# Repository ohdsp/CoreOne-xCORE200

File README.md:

# [Open Hardware DSP Platform](http://www.ohdsp.org)
## CoreOne-xCORE200
### Revision 2.1

---
# README
### Disclaimer
Copyright Paul Janicki 2019

Licensed under the TAPR Open Hardware License (www.tapr.org/OHL)

This documentation is distributed WITHOUT ANY EXPRESS OR IMPLIED WARRANTY, INCLUDING OF MERCHANTABILITY, SATISFACTORY QUALITY AND FITNESS FOR A PARTICULAR PURPOSE.

### What is this repository?

**Quick summary**

This is Open Hardware DSP Platform CoreOne-xCORE200 Module Revision 2.0. 

This is a less cramped XMOS 200 based DSP and mirocontroller PCB design with USB, SPDIF, I2S/TDM, SPI, I2C, and Ethernet connectivity options.

This repository contains the KiCad design files, manufacturing Gerber/drill files, PDF/drawing files, and relevant documenation for this board.

**Changelog**
Revision 2.1 has the following changes over Revision 2.0:
Added better grounding on power connector only, added extra vias.

Revision 2.0 has the following changes over Revision 1.0:
The ST1S40 regualtors have been replaced with RT7285C parts
The CS2100 clock generator has been removed
The TPS3808 reset circut has been replaced with an NCP308 part
There are now components on the bottom layer to reduce cramping
Third I2S connector removed
Added second I2C and second SPI connectors

### What is the project folder structure?
Most folder names are self explanatory. Starting from the top level: \
*CoreOne*
+ *Bill of Materials*  - This contains the bill of materials in CVS, LibreOffice Calc and XML formats
+ *Drawings* - This contains PDF and SVG Schematic and PCB files
+ *Gerbers* - This contains the PCB Gerbers and drill drawings for manufacture, there is also a zip file ready to send to most manufacturers
+ *JPEGs* - JPEGs of top and bottom views from 3D viewer
+ *KiCad* - This contains the original KiCad schematic and PCB design files
+ *Pick and Place* - This contains pick and place files for top and bottom sides
### How do I get set up?

**Summary of set up**

1. Set your self up a directory on a local disk, something simple will make life easier (eg C:\Electronics on Windows as used here), but anywhere will do just fine.
2. Download the Kicad-Libs from [https://github.com/ohdsp/KiCad-Libs](https://github.com/ohdsp/KiCad-Libs) and place in C:\Electronics\Kicad-Libs (or your chosen folder) 
3. Create a OHDSP subdirectory in C:\Electronics (so C:\Electronics\OHDSP)
3. Download this project to C:\Electronics\OHDSP\uDSP
4. Fire up Kicad
5. Open the main project file C:\Electronics\OHDSP\uDSP\KiCad\uDSP.pro
7. Do as you wish with the project, just keep it under the TAPR Open Hardware License.
Note: For library issues see below.

Make sure your git setup doesn't exclude files used in the project (like .LIB files) or things may go wrong down the line.

**KiCad Library Configuration**

Note that libraries are setup using relative paths, if you follow the above instructions things should work just fine. Below is the default library setup.

To setup eeschema component libraries:
From KiCad main window go to menu Tools -> Edit Schematic Symbols. In the new Window go to menu Preferences -> Manage Symbol Libraries.

On the new "Symbol Libraries" window select the "Project Specific Libraries" tab. The "Append Library" and "Remove Library" buttons can be used to add/remove enteries.
The standard setup is:

|   | Active | Nickname        | Library Path                                        | Plugin Type | Options | Description |
|---|--------|-----------------|-----------------------------------------------------|-------------|---------|-------------|
| 1 | Ticked | power           | ${KICAD_SYMBOL_DIR}/power.lib                       | Legacy      | (blank) | (blank)     |
| 2 | Ticked | MyKiCadLibs-Lib | ${KIPRJMOD}/../../../KiCad-Libs/MyKiCadLibs-Lib.lib | Legacy      | (blank) | (blank)     |

${KICAD_SYMBOL_DIR}  is set under the Enviromnet Variable Configuration. Close Symbol Libraries dialogue and go "Preferences" -> "Configure Paths..."

${KICAD_SYMBOL_DIR} is set to C:\Program Files\KiCad\share\kicad\library - this is the default for a KiCad install on the C drive

${KIPRJMOD} is automatically set to the location of the project (.pro file), in this example this would be C:\Electronics\OHDSP\uDSP\KiCad

To setup Pcbnew libraries:
From KiCad main window go to menu Tools -> Edit PCB Footprints. In the new Window go to menu Preferences -> Manage Symbol Libraries.

On the new "Symbol Libraries" window select the "Project Specific Libraries" tab. The "Append Library" and "Remove Library" buttons can be used to add/remove enteries.
The standard setup is:

|   | Active | Nickname               | Library Path                                                  | Plugin Type | Options | Description |
|---|--------|------------------------|---------------------------------------------------------------|-------------|---------|-------------|
| 1 | Ticked | MyKiCadLibs-Footprints | ${KIPRJMOD}/../../../KiCad-Libs/MyKiCadLibs-Footprints.pretty | KiCad       | (blank) | (blank)     |

${KIPRJMOD} is automatically set to the location of the project (.pro file), in this example this would be C:\Electronics\OHDSP\uDSP\KiCad

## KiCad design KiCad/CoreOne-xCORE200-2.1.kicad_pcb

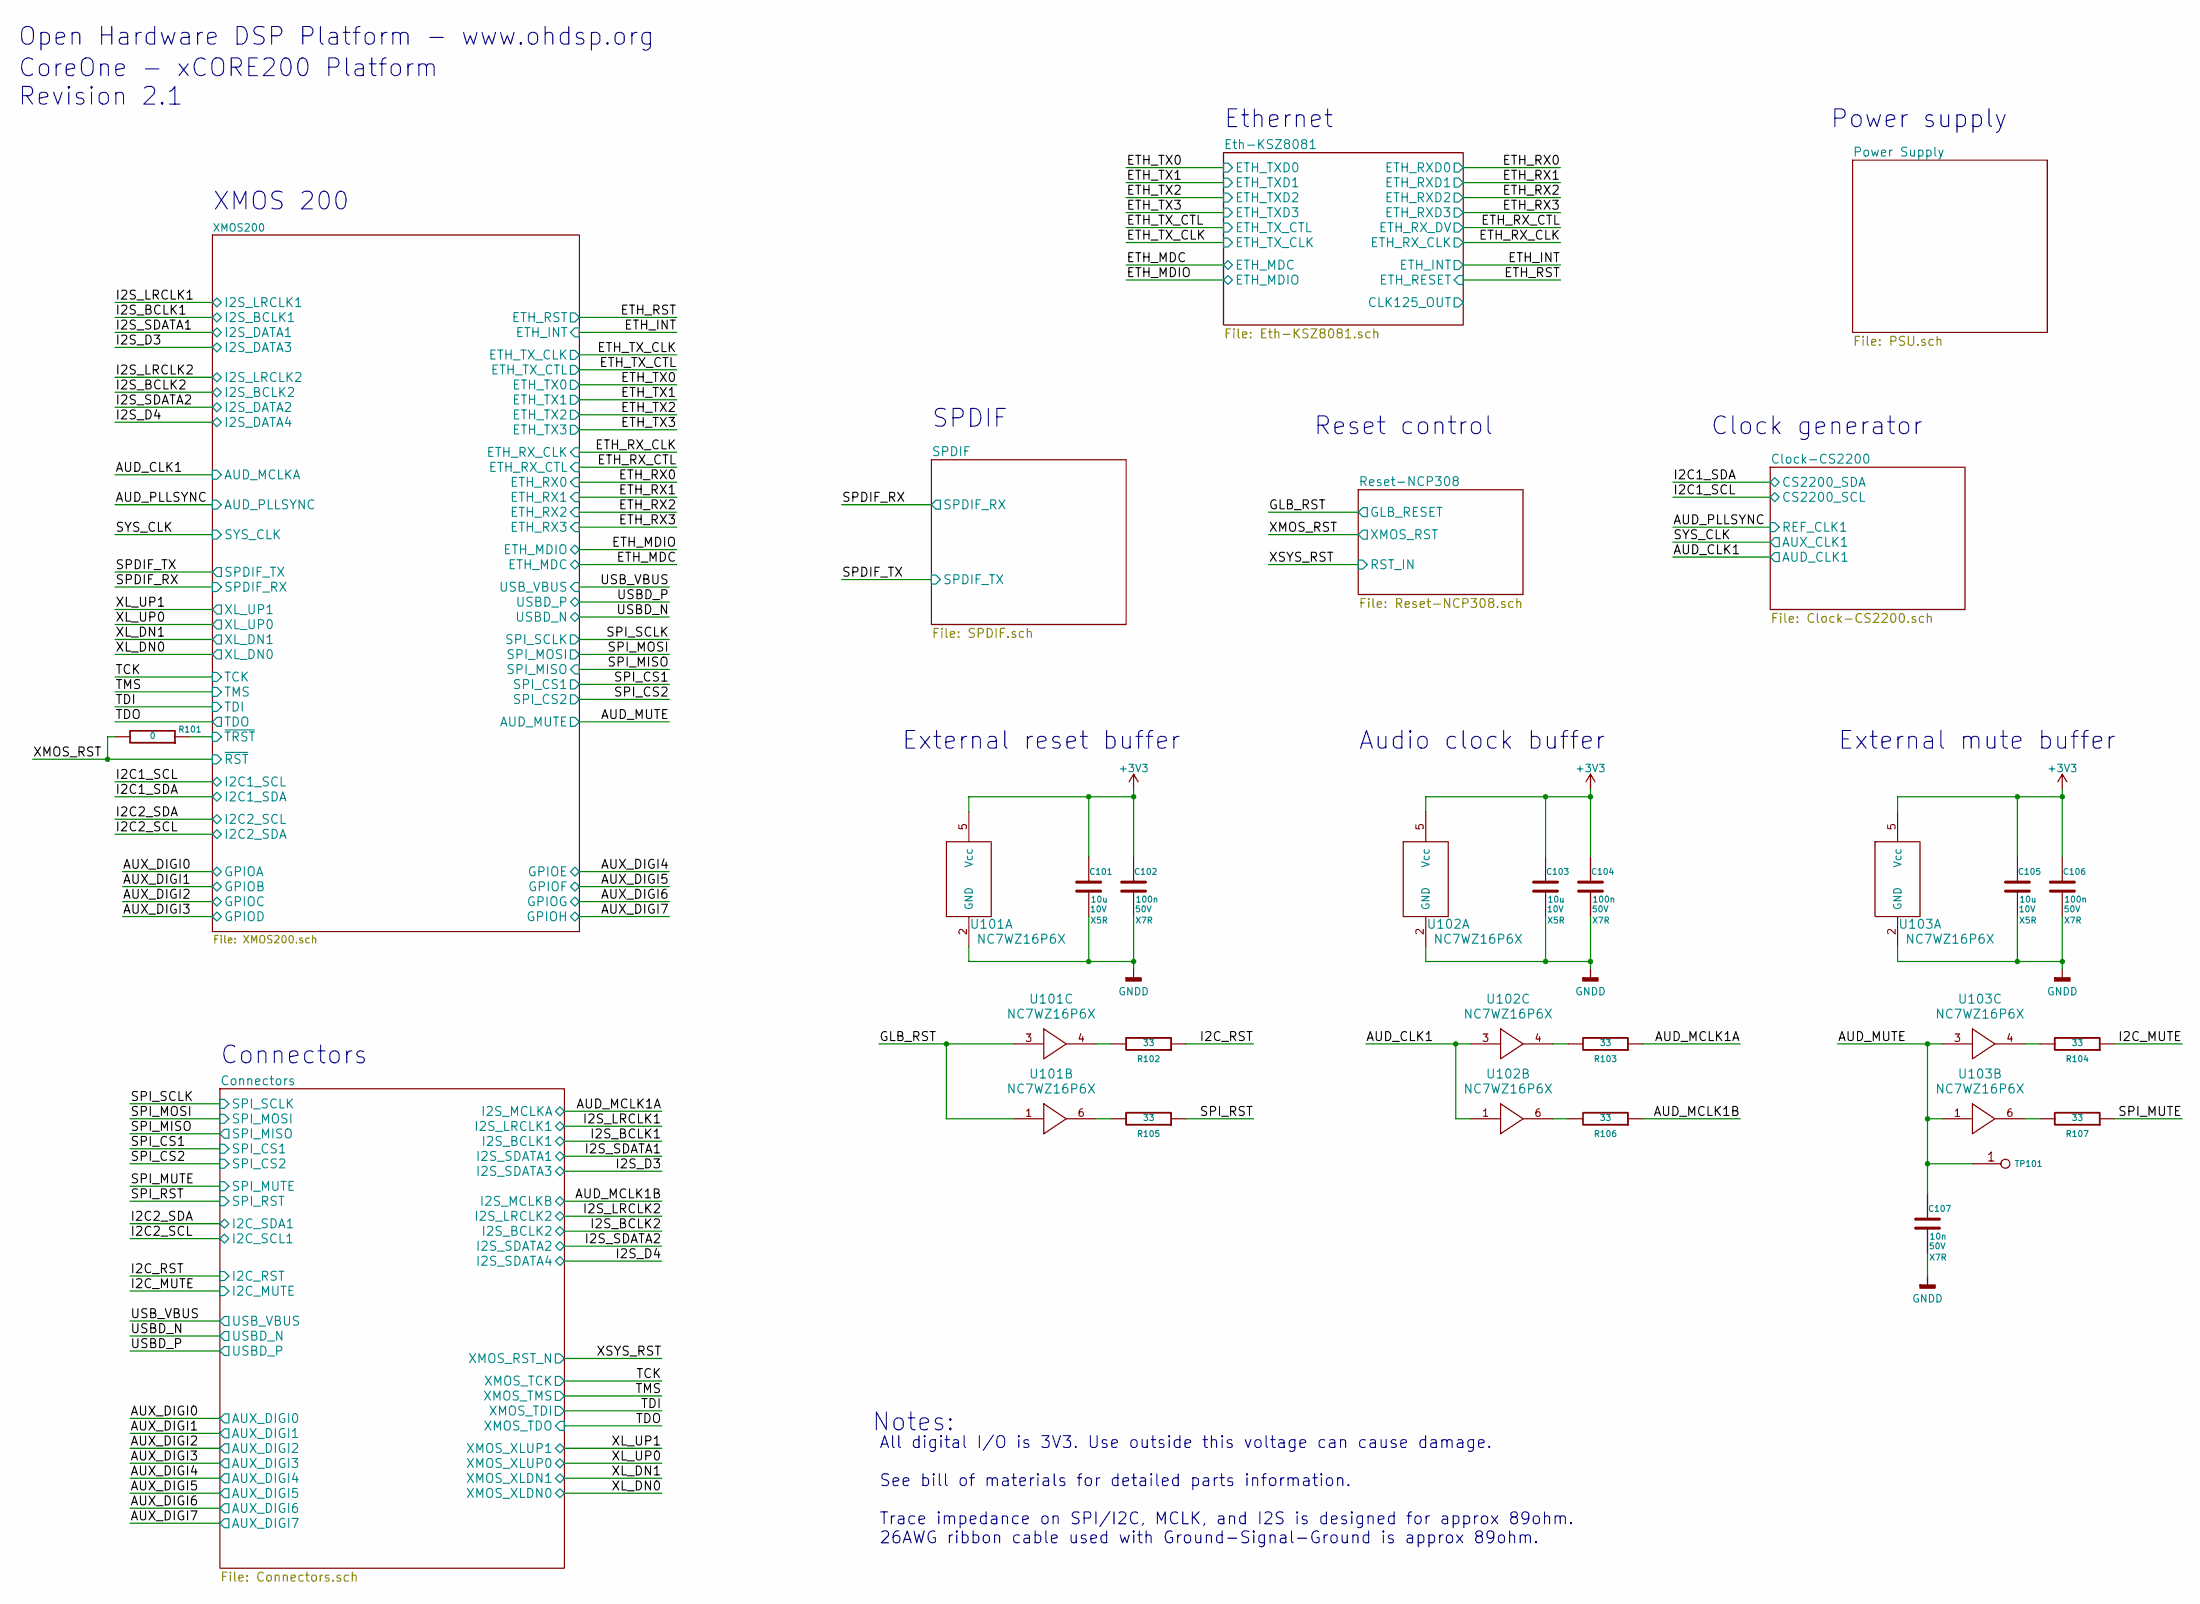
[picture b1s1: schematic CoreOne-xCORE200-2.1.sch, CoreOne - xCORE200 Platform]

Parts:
C101, C103, C105: 10u; SMD-0805; Voltage 10V; Tolerance 20%
C102, C104, C106: 100n; SMD-0805; Voltage 50V; Tolerance 10%
C107: 10n; SMD-0805; Voltage 50V; Tolerance 10%
R101: 0; SMD-0805; Tolerance 1%
R102, R103, R104, R105, R106, R107: 33; SMD-0805; Tolerance 1%
TP101: PIN; TP-2mm
U101, U102, U103: NC7WZ16P6X; IC-SC70-6

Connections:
/AUD_CLK1: U102.1, U102.3; also elsewhere on the board
/AUD_MCLK1A: R103.1; also elsewhere on the board
/AUD_MCLK1B: R106.1; also elsewhere on the board
/AUD_MUTE: C107.1, TP101.1, U103.1, U103.3; also elsewhere on the board
/GLB_RST: U101.1, U101.3; also elsewhere on the board
/I2C_MUTE: R104.1; also elsewhere on the board
/I2C_RST: R102.1; also elsewhere on the board
/SPI_MUTE: R107.1; also elsewhere on the board
/SPI_RST: R105.1; also elsewhere on the board
/XMOS200/~TRST~: R101.1; also elsewhere on the board
/XMOS_RST: R101.2; also elsewhere on the board
GNDD: C101.2, C102.2, C103.2, C104.2, C105.2, C106.2, C107.2, U101.2 (GND), U102.2 (GND), U103.2 (GND); also elsewhere on the board
unnamed: R102.2, U101.4
unnamed: R103.2, U102.4
unnamed: R104.2, U103.4
unnamed: R105.2, U101.6
unnamed: R106.2, U102.6
unnamed: R107.2, U103.6

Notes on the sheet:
Open Hardware DSP Platform - www.ohdsp.org
All digital I/O is 3V3. Use outside this voltage can cause damage. See bill of materials for detailed parts information. Trace impedance on SPI/I2C, MCLK, and I2S is designed for approx 89ohm. 26AWG ribbon cable used with Ground-Signal-Ground is approx 89ohm.
Notes:
CoreOne - xCORE200 Platform Revision 2.1
XMOS 200
Ethernet
Connectors
SPDIF
Reset control
Power supply
Clock generator
External reset buffer
Audio clock buffer
External mute buffer

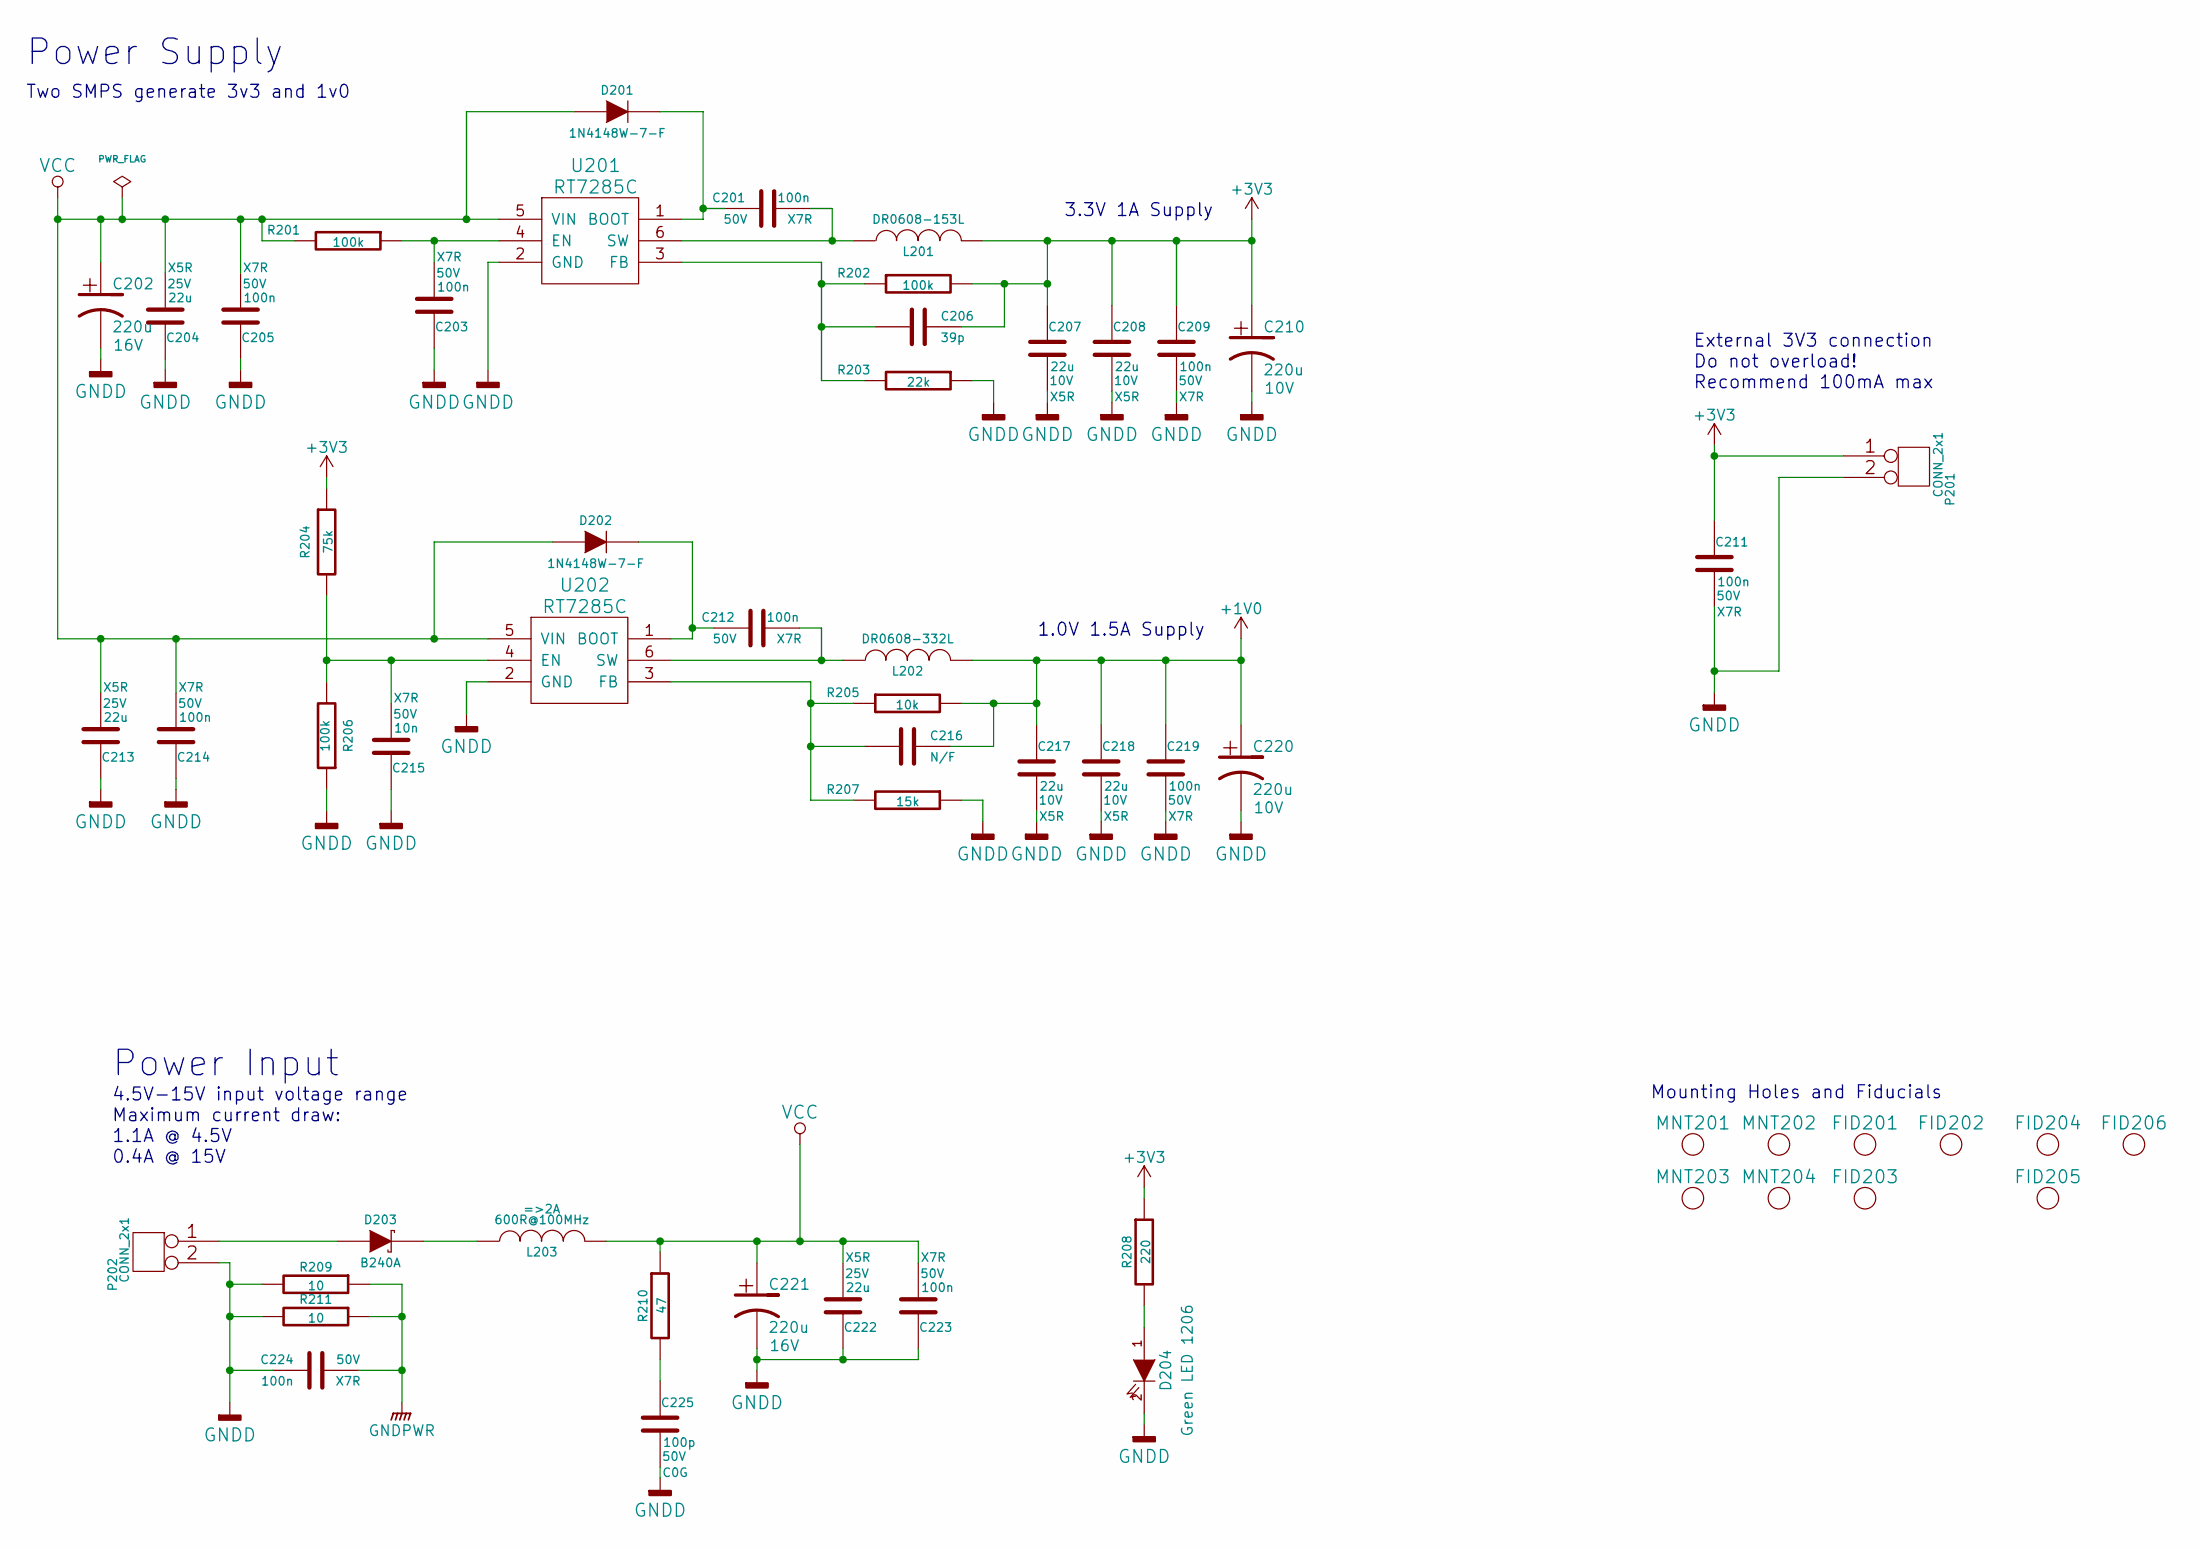
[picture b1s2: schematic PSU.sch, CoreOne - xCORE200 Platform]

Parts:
C201, C203, C205, C209, C211, C212, C214, C219, C223, C224: 100n; SMD-0805; Voltage 50V; Tolerance 10%
C202, C221: 220u; CAP-TH-D6.3mmP2.5mm; Voltage 16V
C204, C213, C222: 22u; SMD-0805; Voltage 25V; Tolerance 20%
C206: 39p; SMD-0805; Voltage 50V; Tolerance 10%
C207, C208, C217, C218: 22u; SMD-0805; Voltage 10V; Tolerance 20%
C210, C220: 220u; CAP-TH-D6.3mmP2.5mm; Voltage 10V
C215: 10n; SMD-0805; Voltage 50V; Tolerance 10%
C216: N/F; SMD-0805; Voltage 50V; Tolerance 10%
C225: 100p; SMD-0805; Voltage 50V; Tolerance 5%
D201, D202: 1N4148W-7-F; DIODE-SOD-123
D203: B240A; DIODE-SMA
D204: Green LED 1206; SMD-1206
FID201, FID202, FID203, FID204, FID205, FID206: MNT_HOLE; FID-1MM-3MM
L201: DR0608-153L; IND-TH-DR0608
L202: DR0608-332L; IND-TH-DR0608
L203: 600R@100MHz; SMD-0805
MNT201, MNT202, MNT203, MNT204: MNT_HOLE; MNT_HOLE_3.2mm
P201: CONN_2x1; CONN_SIL_2_1MM
P202: CONN_2x1; CONN-2WAY-2.54mm-3.81mm-SPACING
R201, R202, R206: 100k; SMD-0805; Tolerance 1%
R203: 22k; SMD-0805; Tolerance 1%
R204: 75k; SMD-0805; Tolerance 1%
R205: 10k; SMD-0805; Tolerance 1%
R207: 15k; SMD-0805; Tolerance 1%
R208: 220; SMD-0805; Tolerance 1%
R209, R211: 10; SMD-0805; Tolerance 1%
R210: 47; SMD-0805; Tolerance 1%
U201, U202: RT7285C; IC-SOT23-6

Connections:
+1V0: C216.1, C217.1, C218.1, C219.1, C220.1, L202.2, R205.2; also elsewhere on the board
GNDD: C202.2, C203.1, C204.1, C205.1, C207.2, C208.2, C209.2, C210.2, C211.2, C213.1, C214.1, C215.1, C217.2, C218.2, C219.2, C220.2, C221.2, C222.1, C223.1, C224.1, C225.2, D204.2 (K), P201.2, P202.2, R203.1, R206.1, R207.1, R209.2, R211.2, U201.2 (GND), U202.2 (GND); also elsewhere on the board
GNDPWR: C224.2, R209.1, R211.1; also elsewhere on the board
unnamed: C201.1, D201.2 (K), U201.1 (BOOT)
unnamed: C201.2, L201.1, U201.6 (SW)
unnamed: C203.2, R201.1, U201.4 (EN)
unnamed: C206.2, R202.1, R203.2, U201.3 (FB)
unnamed: C212.1, D202.2 (K), U202.1 (BOOT)
unnamed: C212.2, L202.1, U202.6 (SW)
unnamed: C215.2, R204.2, R206.2, U202.4 (EN)
unnamed: C216.2, R205.1, R207.2, U202.3 (FB)
unnamed: C225.1, R210.2
unnamed: D203.1 (A), P202.1
unnamed: D203.2 (K), L203.1
unnamed: D204.1 (A), R208.2
VCC: C202.1, C204.2, C205.2, C213.2, C214.2, C221.1, C222.2, C223.2, D201.1 (A), D202.1 (A), L203.2, R201.2, R210.1, U201.5 (VIN), U202.5 (VIN)

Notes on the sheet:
Power Supply
4.5V-15V input voltage range Maximum current draw: 1.1A @ 4.5V 0.4A @ 15V
Power Input
Two SMPS generate 3v3 and 1v0
External 3V3 connection Do not overload! Recommend 100mA max
Mounting Holes and Fiducials
3.3V 1A Supply
1.0V 1.5A Supply

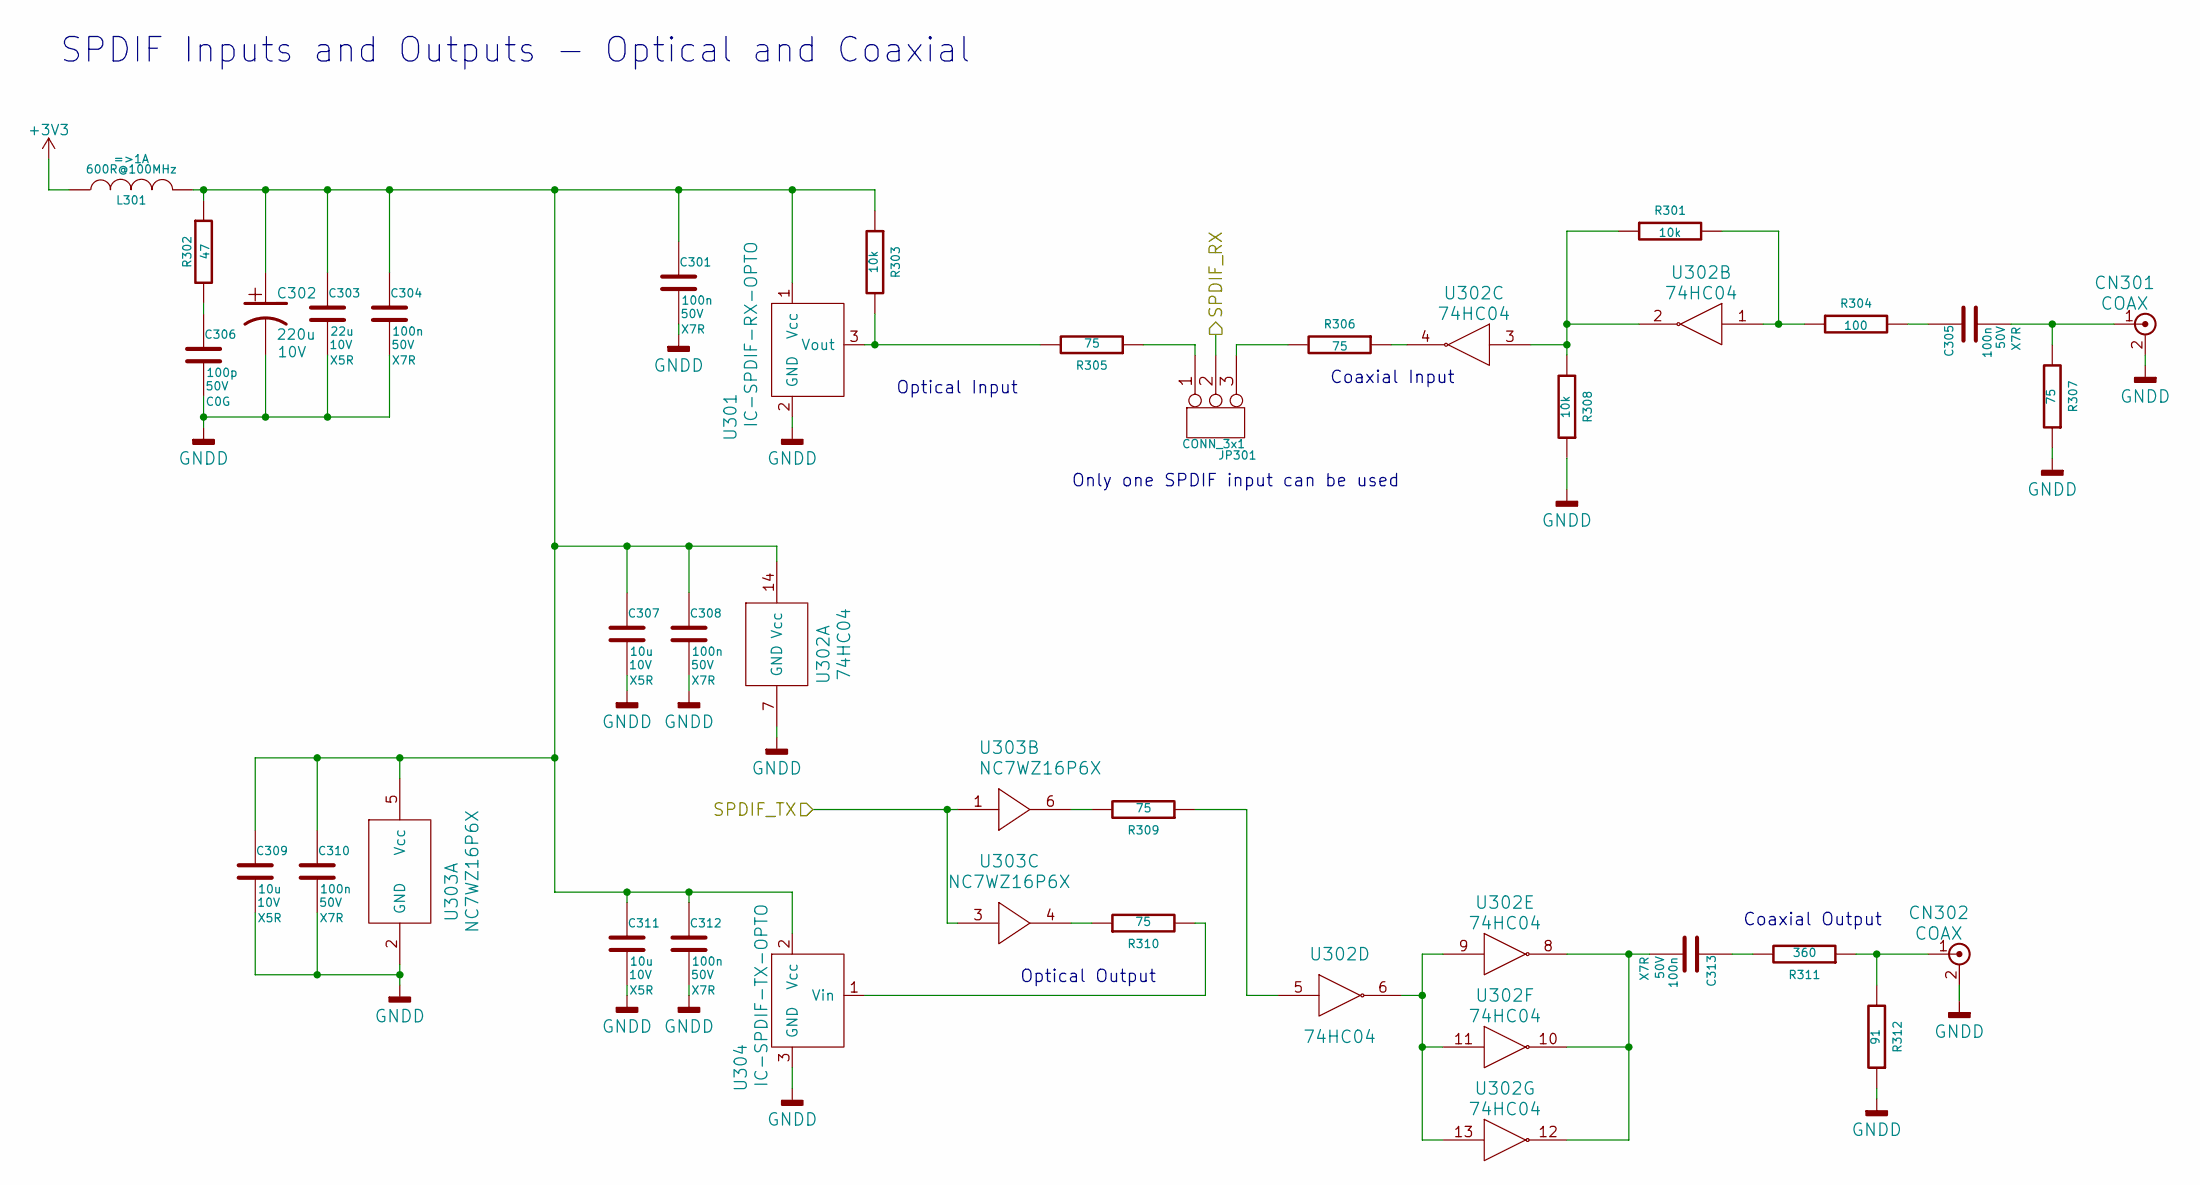
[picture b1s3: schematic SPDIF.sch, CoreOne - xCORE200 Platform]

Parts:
C301, C304, C305, C308, C310, C312, C313: 100n; SMD-0805; Voltage 50V; Tolerance 10%
C302: 220u; CAP-TH-D6.3mmP2.5mm; Voltage 10V
C303: 22u; SMD-0805; Voltage 10V; Tolerance 20%
C306: 100p; SMD-0805; Voltage 50V; Tolerance 5%
C307, C309, C311: 10u; SMD-0805; Voltage 10V; Tolerance 20%
CN301, CN302: COAX; CONN_SIL_2_1MM
JP301: CONN_3x1; CONN_SIL_3_1MM
L301: 600R@100MHz; SMD-0805
R301, R303, R308: 10k; SMD-0805; Tolerance 1%
R302: 47; SMD-0805; Tolerance 1%
R304: 100; SMD-0805; Tolerance 1%
R305, R306, R307, R309, R310: 75; SMD-0805; Tolerance 1%
R311: 360; SMD-0805; Tolerance 1%
R312: 91; SMD-0805; Tolerance 1%
U301: IC-SPDIF-RX-OPTO; IC_SPDIF_OPTO
U302: 74HC04; IC_SOIC_14
U303: NC7WZ16P6X; IC-SC70-6
U304: IC-SPDIF-TX-OPTO; IC_SPDIF_OPTO

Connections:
/SPDIF_RX: JP301.2; also elsewhere on the board
/SPDIF_TX: U303.1, U303.3; also elsewhere on the board
GNDD: C301.2, C302.2, C303.2, C304.2, C306.2, C307.2, C308.2, C309.2, C310.2, C311.2, C312.2, CN301.2, CN302.2, R307.1, R308.1, R312.1, U301.2 (GND), U302.7 (GND), U303.2 (GND), U304.3 (GND); also elsewhere on the board
unnamed: C301.1, C302.1, C303.1, C304.1, C307.1, C308.1, C309.1, C310.1, C311.1, C312.1, L301.2, R302.1, R303.1, U301.1 (Vcc), U302.14 (Vcc), U303.5 (Vcc), U304.2 (Vcc)
unnamed: C305.1, R304.2
unnamed: C305.2, CN301.1, R307.2
unnamed: C306.1, R302.2
unnamed: C313.1, R311.2
unnamed: C313.2, U302.8, U302.10, U302.12
unnamed: CN302.1, R311.1, R312.2
unnamed: JP301.1, R305.1
unnamed: JP301.3, R306.2
unnamed: R301.1, R308.2, U302.2, U302.3
unnamed: R301.2, R304.1, U302.1
unnamed: R303.2, R305.2, U301.3 (Vout)
unnamed: R306.1, U302.4
unnamed: R309.1, U302.5
unnamed: R309.2, U303.6
unnamed: R310.1, U303.4
unnamed: R310.2, U304.1 (Vin)
unnamed: U302.6, U302.9, U302.11, U302.13

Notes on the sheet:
SPDIF Inputs and Outputs - Optical and Coaxial
Optical Input
Coaxial Input
Optical Output
Coaxial Output
Only one SPDIF input can be used

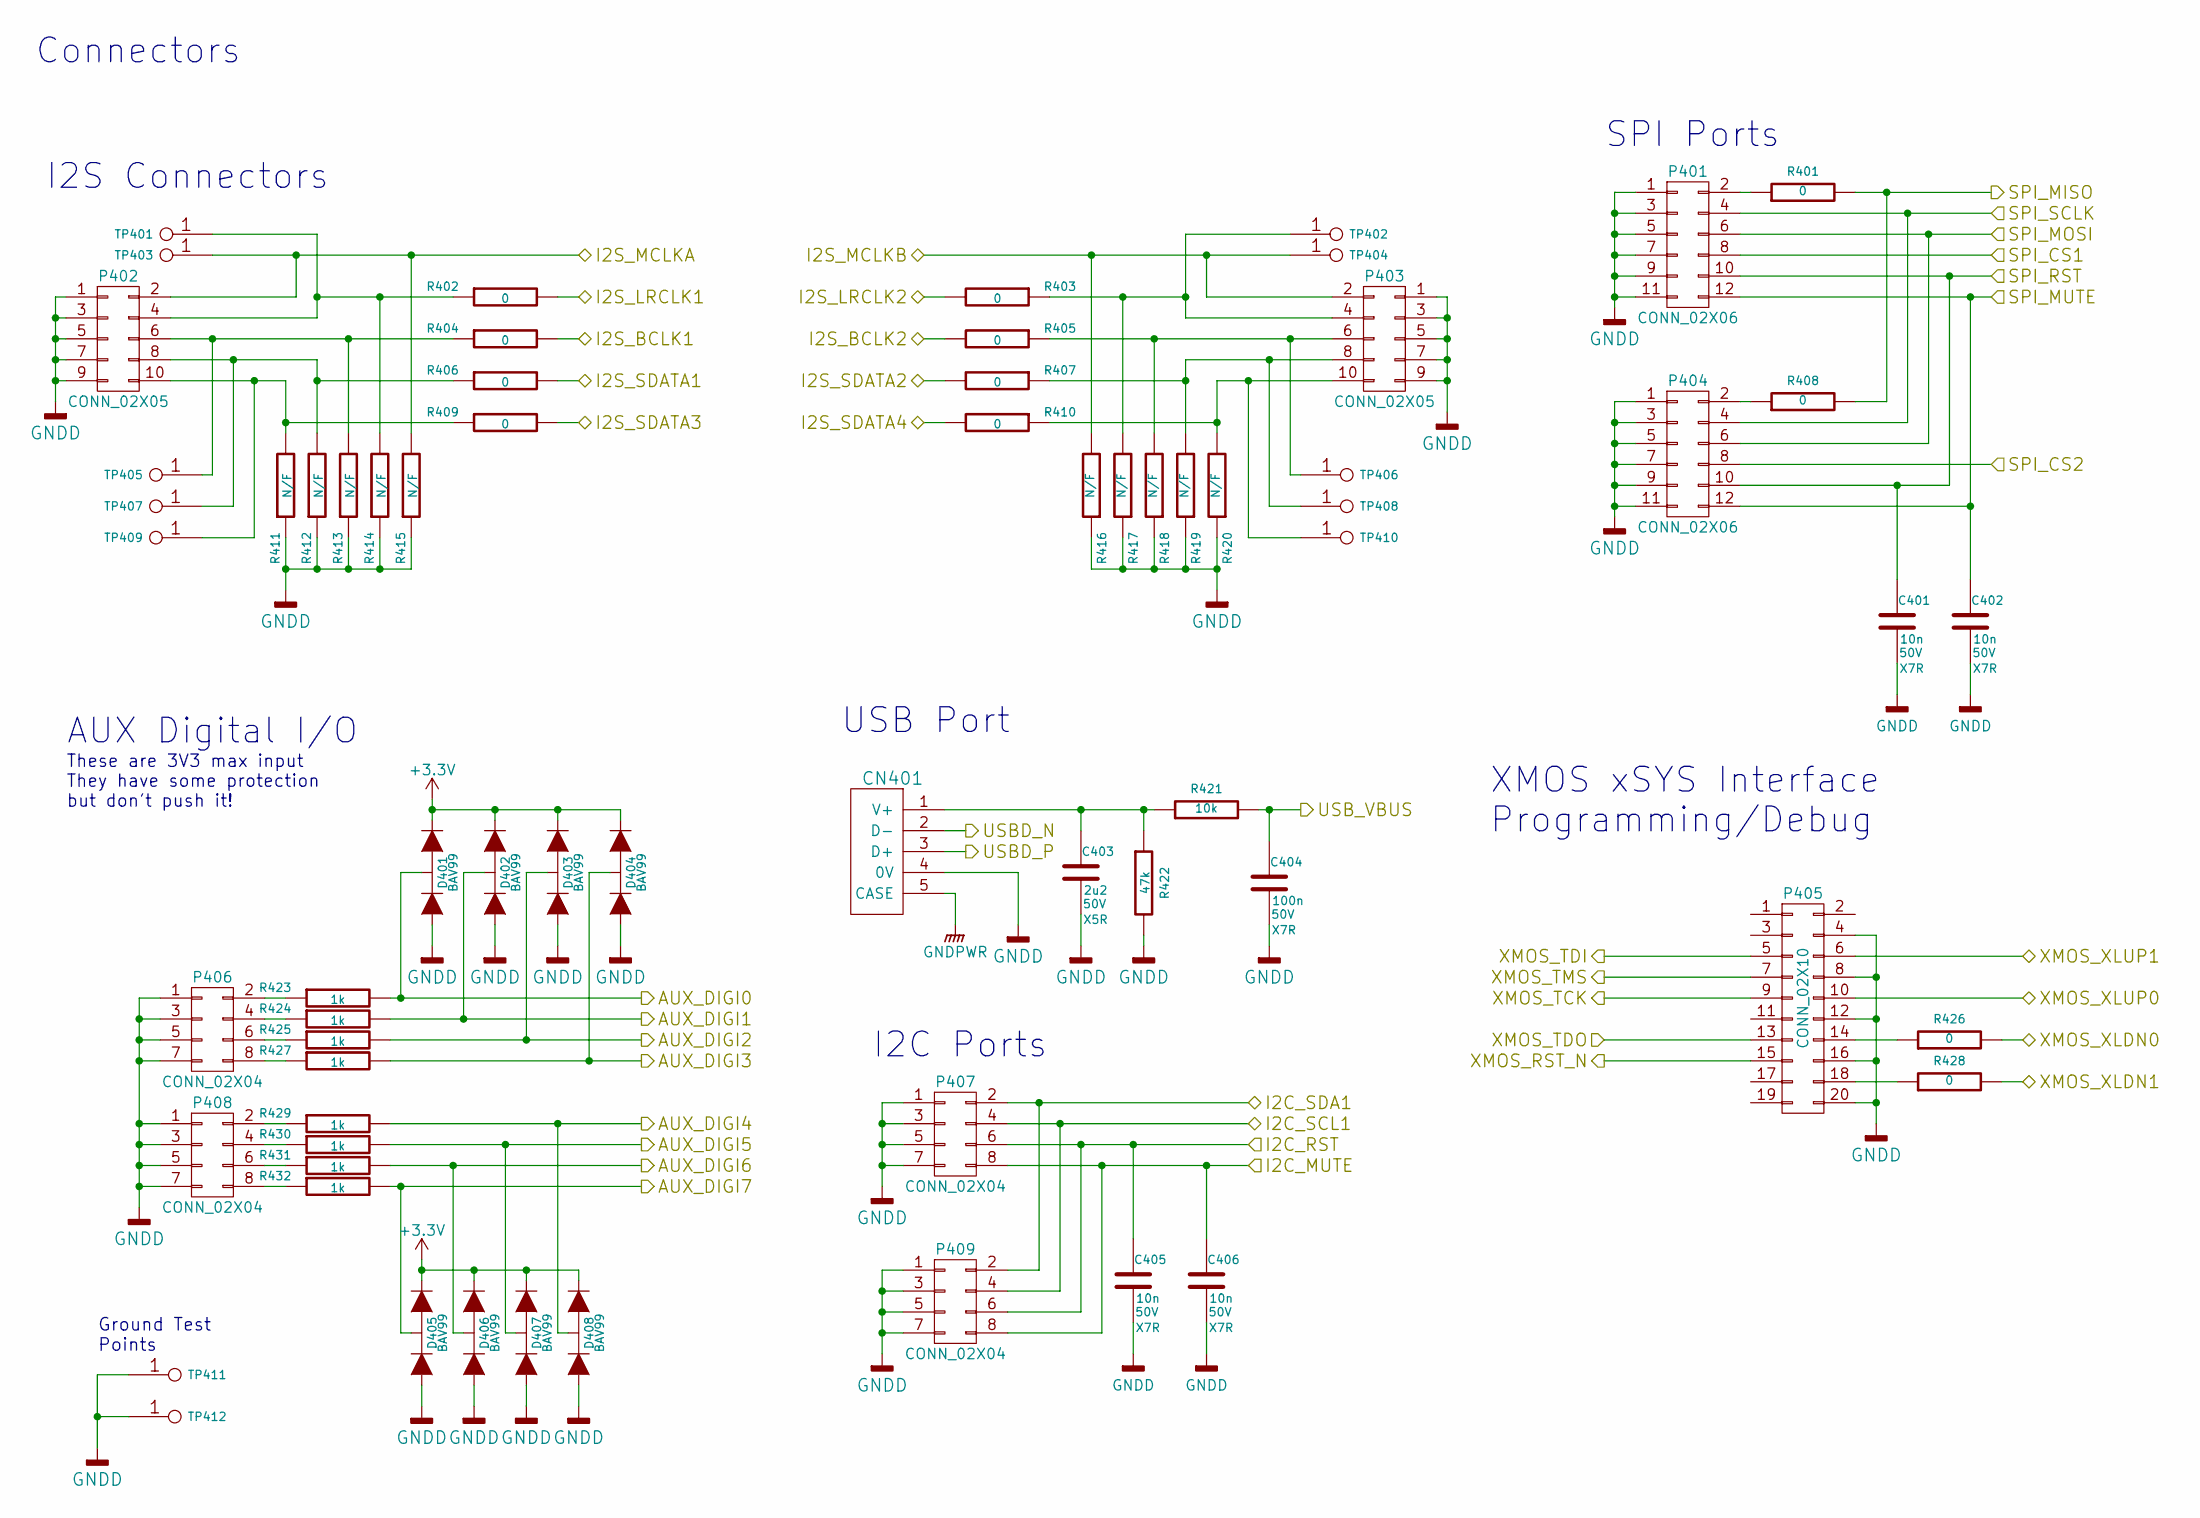
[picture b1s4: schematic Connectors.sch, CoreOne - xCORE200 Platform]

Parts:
C401, C402, C405, C406: 10n; SMD-0805; Voltage 50V; Tolerance 10%
C403: 2u2; SMD-0805; Voltage 50V; Tolerance 10%
C404: 100n; SMD-0805; Voltage 50V; Tolerance 10%
CN401: CONN-USB-B-61729; CONN-USB-B-61729-0010
D401, D402, D403, D404, D405, D406, D407, D408: BAV99; IC-SOT23
P401, P404: CONN_02X06; CONN_DIL_2X6_BOX_1MM
P402, P403: CONN_02X05; CONN_DIL_2X5_BOX_1MM
P405: CONN_02X10; CONN_DIL_2X10_BOX_1MM
P406, P408: CONN_02X04; CONN_DIL_2X04
P407, P409: CONN_02X04; CONN_DIL_2X4_BOX_1MM
R401, R402, R403, R404, R405, R406, R407, R408, R409, R410, R426, R428: 0; SMD-0805; Tolerance 1%
R411, R412, R413, R414, R415, R416, R417, R418, R419, R420: N/F; SMD-0805; Tolerance 1%
R421: 10k; SMD-0805; Tolerance 1%
R422: 47k; SMD-0805; Tolerance 1%
R423, R424, R425, R427, R429, R430, R431, R432: 1k; SMD-0805; Tolerance 1%
TP401, TP402, TP403, TP404, TP405, TP406, TP407, TP408, TP409, TP410, TP411, TP412: PIN; TP-TH-1mm

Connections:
/AUD_MCLK1A: P402.2, R415.2, TP403.1; also elsewhere on the board
/AUD_MCLK1B: P403.2, R416.2, TP404.1; also elsewhere on the board
/AUX_DIGI0: D401.3 (K1A2), R423.2; also elsewhere on the board
/AUX_DIGI1: D402.3 (K1A2), R424.2; also elsewhere on the board
/AUX_DIGI2: D403.3 (K1A2), R425.2; also elsewhere on the board
/AUX_DIGI3: D404.3 (K1A2), R427.2; also elsewhere on the board
/AUX_DIGI4: D408.3 (K1A2), R429.2; also elsewhere on the board
/AUX_DIGI5: D407.3 (K1A2), R430.2; also elsewhere on the board
/AUX_DIGI6: D406.3 (K1A2), R431.2; also elsewhere on the board
/AUX_DIGI7: D405.3 (K1A2), R432.2; also elsewhere on the board
/I2C2_SCL: P407.4, P409.4; also elsewhere on the board
/I2C2_SDA: P407.2, P409.2; also elsewhere on the board
/I2C_MUTE: C406.1, P407.8, P409.8; also elsewhere on the board
/I2C_RST: C405.1, P407.6, P409.6; also elsewhere on the board
/I2S_BCLK1: R404.2; also elsewhere on the board
/I2S_BCLK2: R405.2; also elsewhere on the board
/I2S_D3: R409.2; also elsewhere on the board
/I2S_D4: R410.2; also elsewhere on the board
/I2S_LRCLK1: R402.2; also elsewhere on the board
/I2S_LRCLK2: R403.2; also elsewhere on the board
/I2S_SDATA1: R406.2; also elsewhere on the board
/I2S_SDATA2: R407.2; also elsewhere on the board
/SPI_CS1: P401.8; also elsewhere on the board
/SPI_CS2: P404.8; also elsewhere on the board
/SPI_MISO: R401.2, R408.2; also elsewhere on the board
/SPI_MOSI: P401.6, P404.6; also elsewhere on the board
/SPI_MUTE: C402.1, P401.12, P404.12; also elsewhere on the board
/SPI_RST: C401.1, P401.10, P404.10; also elsewhere on the board
/SPI_SCLK: P401.4, P404.4; also elsewhere on the board
/TCK: P405.9; also elsewhere on the board
/TDI: P405.5; also elsewhere on the board
/TDO: P405.13; also elsewhere on the board
/TMS: P405.7; also elsewhere on the board
/USBD_N: CN401.2 (D-); also elsewhere on the board
/USBD_P: CN401.3 (D+); also elsewhere on the board
/USB_VBUS: C404.1, R421.2; also elsewhere on the board
/XL_DN0: R426.2; also elsewhere on the board
/XL_DN1: R428.2; also elsewhere on the board
/XL_UP0: P405.10; also elsewhere on the board
/XL_UP1: P405.6; also elsewhere on the board
/XSYS_RST: P405.15; also elsewhere on the board
GNDD: C401.2, C402.2, C403.2, C404.2, C405.2, C406.2, CN401.4 (0V), D401.1 (A1), D402.1 (A1), D403.1 (A1), D404.1 (A1), D405.1 (A1), D406.1 (A1), D407.1 (A1), D408.1 (A1), P401.1, P401.3, P401.5, P401.7, P401.9, P401.11, P402.1, P402.3, P402.5, P402.7, P402.9, P403.1, P403.3, P403.5, P403.7, P403.9, P404.1, P404.3, P404.5, P404.7, P404.9, P404.11, P405.4, P405.8, P405.12, P405.16, P405.20, P406.1, P406.3, P406.5, P406.7, P407.1, P407.3, P407.5, P407.7, P408.1, P408.3, P408.5, P408.7, P409.1, P409.3, P409.5, P409.7, R411.1, R412.1, R413.1, R414.1, R415.1, R416.1, R417.1, R418.1, R419.1, R420.1, R422.2, TP411.1, TP412.1; also elsewhere on the board
GNDPWR: CN401.5 (CASE); also elsewhere on the board
unnamed: C403.1, CN401.1 (V+), R421.1, R422.1
unnamed: P401.2, R401.1
unnamed: P402.4, R402.1, R414.2, TP401.1
unnamed: P402.6, R404.1, R413.2, TP405.1
unnamed: P402.8, R406.1, R412.2, TP407.1
unnamed: P402.10, R409.1, R411.2, TP409.1
unnamed: P403.4, R403.1, R417.2, TP402.1
unnamed: P403.6, R405.1, R418.2, TP406.1
unnamed: P403.8, R407.1, R419.2, TP408.1
unnamed: P403.10, R410.1, R420.2, TP410.1
unnamed: P404.2, R408.1
unnamed: P405.14, R426.1
unnamed: P405.18, R428.1
unnamed: P406.2, R423.1
unnamed: P406.4, R424.1
unnamed: P406.6, R425.1
unnamed: P406.8, R427.1
unnamed: P408.2, R429.1
unnamed: P408.4, R430.1
unnamed: P408.6, R431.1
unnamed: P408.8, R432.1

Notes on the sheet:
XMOS xSYS Interface Programming/Debug
AUX Digital I/O
I2S Connectors
These are 3V3 max input They have some protection but don't push it!
Ground Test Points
SPI Ports
Connectors
I2C Ports
USB Port

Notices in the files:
KiCad/CoreOne-xCORE200-2.1.kicad_pcb:
Copyright ©
Licensed under TAPR OHL
